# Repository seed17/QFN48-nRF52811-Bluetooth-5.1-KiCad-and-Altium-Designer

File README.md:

# QFN48-nRF52811-Bluetooth-5.1-KiCad and Altium

The original schematic and files were designed and downloaded as Altium designer files. Afte they were edited to make the dev board, this repo was used: https://github.com/thesourcerer8/altium2kicad to convert the altium designer files from altium to KiCad. Then, these files still neded editing in KiCad, eventyally leading to the filal KiCad file. It is reccomended to use the Altium files if you intend to print of use the board, but if you insist on KiCad, just check for errors (unconnected pads) on the pcb, if you spot any fix ut, email me for the fix or open an issue and you will be good to go. I would be more than happy if anyone checked the KiCad files and aproved their functionality, or design the board from the beggining for KiCad. Its not very complex circuit, last time i checked the KiCad pcb was file, wihtout weird connections

Dc-Dc schematic From datasheet: 

Edited Altium Designer PCB [dc-dc schematic] as a dev board, 3D view: 

Edited Altium Designer PCB [dc-dc schematic] as a dev board, 2D view: 

Edited KiCad PCB, 2D 

Edited KiCad PCB, 3D 

REFERENCE LAYOUT FOUND HERE [QFN48]: https://www.nordicsemi.com/?sc_itemid=%7B7CBDF55C-9745-4A7D-A491-5B66AE9454B6%7D

Questions? issues? email me: basilisvirus@hotmail.com

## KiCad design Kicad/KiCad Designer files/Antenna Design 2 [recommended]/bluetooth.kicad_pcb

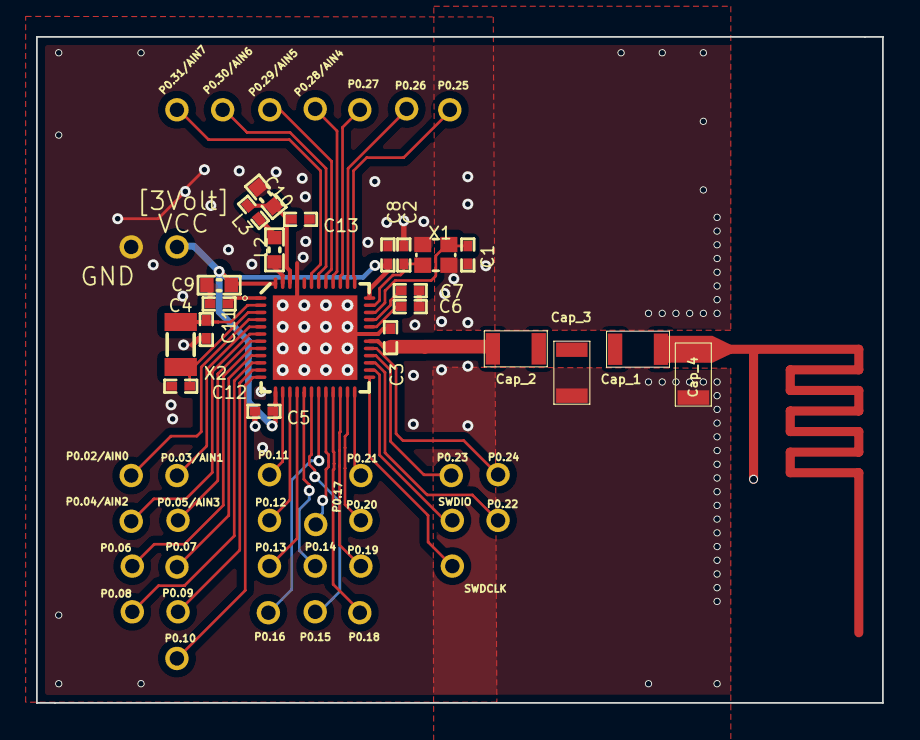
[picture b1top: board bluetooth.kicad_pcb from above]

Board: 2 copper layers, 47.0 x 37.0 mm, 56 parts (0 on the bottom side), 13 nets.

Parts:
C1, C2, C3, C4, C5, C7, C8, C11, C12: CAPC1005X04L
C6, C13: Not mounted; CAPC1005X04L
C9, C10: CAPC1608X06L
Cap_1, Cap_2, Cap_3, Cap_4: 1206_cap_smd
L2: INDC1608X06L
L3: INDC1005X04L
U1: Multi-protocol Bluetooth Low Energy, IEEE 802.15.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; QFN40P600X600X90-48N
U1#2, U2, U3, U4, U5, U6, U7, U8, U9, U10, U11, U12, U13, U14, U15, U16, U17, U18, U19, U20, U21, U23, U24, U25, U26, U27, U28, U29, U30, U31, U32, U33, U102, U102#2: O; Ο
X1: BT-XTAL_2016
X2: XTAL_3215

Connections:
DEC1: C4.1, U1.1
DEC2: C6.2, U1.32
DEC3: C7.1, U1.33
DEC4: C10.2, C13.1, L3.1, U1.46
GND: C1.2, C2.2, C3.1, C4.2, C5.2, C6.1, C7.2, C8.2, C9.2, C10.1, C11.2, C12.2, C13.2, Cap_3.1, Cap_3.2, Cap_4.1, Cap_4.2, U1.31, U1.45, U1.49, U26.GND, X1.2, X1.4
unnamed: U102.1, U102#2.1
NetL2_1: L2.1, L3.2
NetL2_2: L2.2, U1.47
P0.00/XL1: C11.1, U1.2, X2.1
P0.01/XL2: C12.1, U1.3, X2.2
VDD_NRF: C5.1, C8.1, C9.1, U1.13, U1.36, U1.48
XC1: C1.1, U1.34, X1.1
XC2: C2.1, U1.35, X1.3

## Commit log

2019-07-06 added all files
2019-07-06 added gerber files
2019-07-07 added MPN to bill of materials
2019-07-07 added pdf3D
2019-07-07 added step 3D
2019-07-07 added KiCad Support and files
2019-07-07 fixed KiCad pcb bugs and errors.
2019-07-21 added antenna design log
2019-07-21 added antenna to main pcb
2019-07-21 re-exported and renewed kicad gerber
2019-07-22 changed Documentation
2019-07-23 changed details
2019-07-25 changed pcb position to the center of the pcbnew
2019-07-25 added f.silk and f.crtYd info from altium, added BOM, renewed Gerber, created assembly drawing, fixed pick & place files
2019-07-26 added panel D1, D2 extraction
2019-07-26 fixed Design 1,2 ground plane. Do not change the GND plane fill on the Design1&2 panel
2019-07-26 fixed schematic of Design 1_2 and renewed gerber.
2019-07-29 changed bom
2019-08-09 minor changes
2019-08-30 changed name
